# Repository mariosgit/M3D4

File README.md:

# M3D4

Majo's Mega Mixer Digital 4 devices. Simple.

# Status

Miniboard to test with FreeDSP. @alpha, not tested.

# What's this

Just another mixer thing.

# Cost

| part | euro | ... | # | sum |
|---|---|---|---|---|
| C108 | 2 | | 4 | 8
| SRC419x | 6,42  | SRC | 8 | 52 |
| ADAU1701 | 8,47 | DSP | 1 | 9 |
| sum | | | | **69** |

# Refs

CM108 symbol https://github.com/islandcontroller/fiberaudio-108

# License

### Hardware

<p xmlns:cc="http://creativecommons.org/ns#" >This work is licensed under <a href="https://creativecommons.org/licenses/by-nc-sa/4.0/?ref=chooser-v1" target="_blank" rel="license noopener noreferrer" style="display:inline-block;">CC BY-NC-SA 4.0</a></p>

### Software

MIT

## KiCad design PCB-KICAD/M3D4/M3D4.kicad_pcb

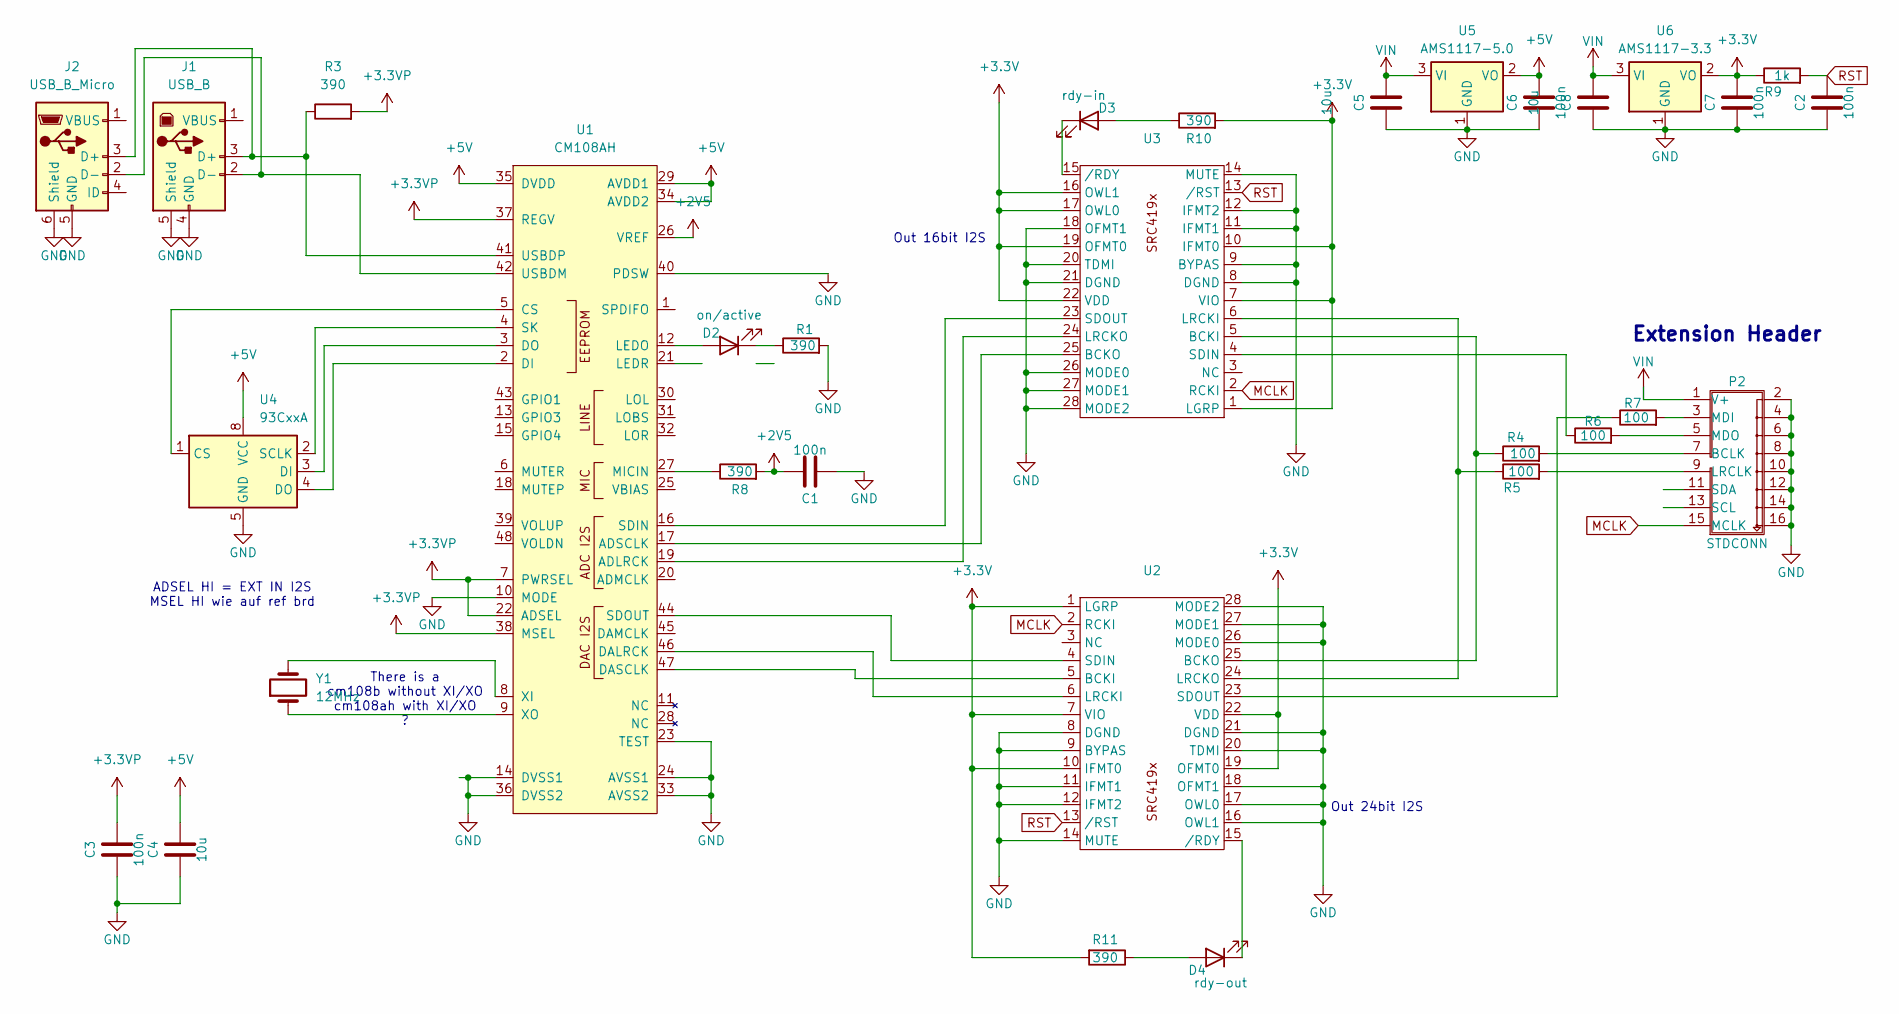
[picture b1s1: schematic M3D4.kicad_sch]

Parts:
C1, C2, C3, C6, C7: 100n; C_0603_1608Metric_Pad1.08x0.95mm_HandSolder
C4, C5: 10u; C_0603_1608Metric_Pad1.08x0.95mm_HandSolder
C8: 10u; C_1206_3216Metric_Pad1.33x1.80mm_HandSolder
D2: on/active; LED_0603_1608Metric_Pad1.05x0.95mm_HandSolder
D3: rdy-in; LED_0603_1608Metric_Pad1.05x0.95mm_HandSolder
D4: rdy-out; LED_0603_1608Metric_Pad1.05x0.95mm_HandSolder
J1: USB_B; USB_B_Lumberg_2411_02_Horizontal
J2: USB_B_Micro; USB_Micro-B_Amphenol_10103594-0001LF_Horizontal
P2: STDCONN; PinHeader_2x08_P2.54mm_Vertical
R1, R3, R8, R10, R11: 390; R_0603_1608Metric_Pad0.98x0.95mm_HandSolder
R4, R5, R6, R7: 100; R_0603_1608Metric_Pad0.98x0.95mm_HandSolder
R9: 1k; R_0603_1608Metric_Pad0.98x0.95mm_HandSolder
U1: CM108AH; LQFP-48_7x7mm_P0.5mm
U2, U3: SSOP-28_3.9x9.9mm_P0.635mm
U4: 93CxxA; SOIC-8-N7_3.9x4.9mm_P1.27mm
U5: AMS1117-5.0; SOT-223-3_TabPin2
U6: AMS1117-3.3; SOT-223-3_TabPin2
Y1: 12MHz; Crystal_SMD_HC49-SD_HandSoldering

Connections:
+2V5: C1.1, R8.2, U1.26 (VREF)
+3.3V: C7.1, R9.1, R10.2, R11.2, U2.1 (LGRP), U2.7 (VIO), U2.10 (IFMT0), U2.19 (OFMT0), U2.22 (VDD), U3.1 (LGRP), U3.7 (VIO), U3.10 (IFMT0), U3.16 (OWL1), U3.17 (OWL0), U3.19 (OFMT0), U3.22 (VDD), U6.2 (VO)
+3.3VP: C3.1, R3.2, U1.7 (PWRSEL), U1.22 (ADSEL), U1.37 (REGV), U1.38 (MSEL)
+5V: C4.1, C6.1, U1.29 (AVDD1), U1.34 (AVDD2), U1.35 (DVDD), U4.8 (VCC), U5.2 (VO)
GND: C1.2, C2.2, C3.2, C4.2, C5.2, C6.2, C7.2, C8.2, J1.4 (GND), J1.5 (Shield), J2.5 (GND), J2.6 (Shield), P2.2 (GND), P2.4 (GND), P2.6 (GND), P2.8 (GND), P2.10 (GND), P2.12 (GND), P2.14 (GND), P2.16 (GND), R1.2, U1.10 (MODE), U1.14 (DVSS1), U1.23 (TEST), U1.24 (AVSS1), U1.33 (AVSS2), U1.36 (DVSS2), U1.40 (PDSW), U2.8 (DGND), U2.9 (BYPAS), U2.11 (IFMT1), U2.12 (IFMT2), U2.14 (MUTE), U2.16 (OWL1), U2.17 (OWL0), U2.18 (OFMT1), U2.20 (TDMI), U2.21 (DGND), U2.26 (MODE0), U2.27 (MODE1), U2.28 (MODE2), U3.8 (DGND), U3.9 (BYPAS), U3.11 (IFMT1), U3.12 (IFMT2), U3.14 (MUTE), U3.18 (OFMT1), U3.20 (TDMI), U3.21 (DGND), U3.26 (MODE0), U3.27 (MODE1), U3.28 (MODE2), U4.5 (GND), U5.1 (GND), U6.1 (GND)
MCLK: P2.15 (MCLK), U2.2 (RCKI), U3.2 (RCKI)
unnamed: D2.2 (A), U1.12 (LEDO)
unnamed: D2.1 (K), R1.1
unnamed: D3.2 (A), R10.1
unnamed: D3.1 (K), U3.15 (/RDY)
unnamed: D4.2 (A), R11.1
unnamed: D4.1 (K), U2.15 (/RDY)
unnamed: J1.3 (D+), J2.3 (D+), R3.1, U1.41 (USBDP)
unnamed: J1.2 (D-), J2.2 (D-), U1.42 (USBDM)
unnamed: P2.7 (BCLK), R4.2
unnamed: P2.9 (LRCLK), R5.2
unnamed: P2.3 (MDI), R7.2
unnamed: P2.5 (MDO), R6.2
unnamed: U1.19 (ADLRCK), U3.24 (LRCKO)
unnamed: U1.17 (ADSCLK), U3.25 (BCKO)
unnamed: U1.5 (CS), U4.1 (CS)
unnamed: U1.46 (DALRCK), U2.6 (LRCKI)
unnamed: U1.47 (DASCLK), U2.5 (BCKI)
unnamed: U1.2 (DI), U4.4 (DO)
unnamed: U1.3 (DO), U4.3 (DI)
unnamed: R8.1, U1.27 (MICIN)
unnamed: U1.16 (SDIN), U3.23 (SDOUT)
unnamed: U1.44 (SDOUT), U2.4 (SDIN)
unnamed: U1.4 (SK), U4.2 (SCLK)
unnamed: U1.8 (XI), Y1.2
unnamed: U1.9 (XO), Y1.1
unnamed: R4.1, U2.25 (BCKO), U3.5 (BCKI)
unnamed: R5.1, U2.24 (LRCKO), U3.6 (LRCKI)
unnamed: R7.1, U2.23 (SDOUT)
unnamed: R6.1, U3.4 (SDIN)
RST: C2.1, R9.2, U2.13 (/RST), U3.13 (/RST)
VIN: C5.1, C8.1, P2.1 (V+), U5.3 (VI), U6.3 (VI)

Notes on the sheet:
Out 16bit I2S
ADSEL HI = EXT IN I2S MSEL HI wie auf ref brd
Extension Header
There is a cm108b without XI/XO cm108ah with XI/XO ?
Out 24bit I2S

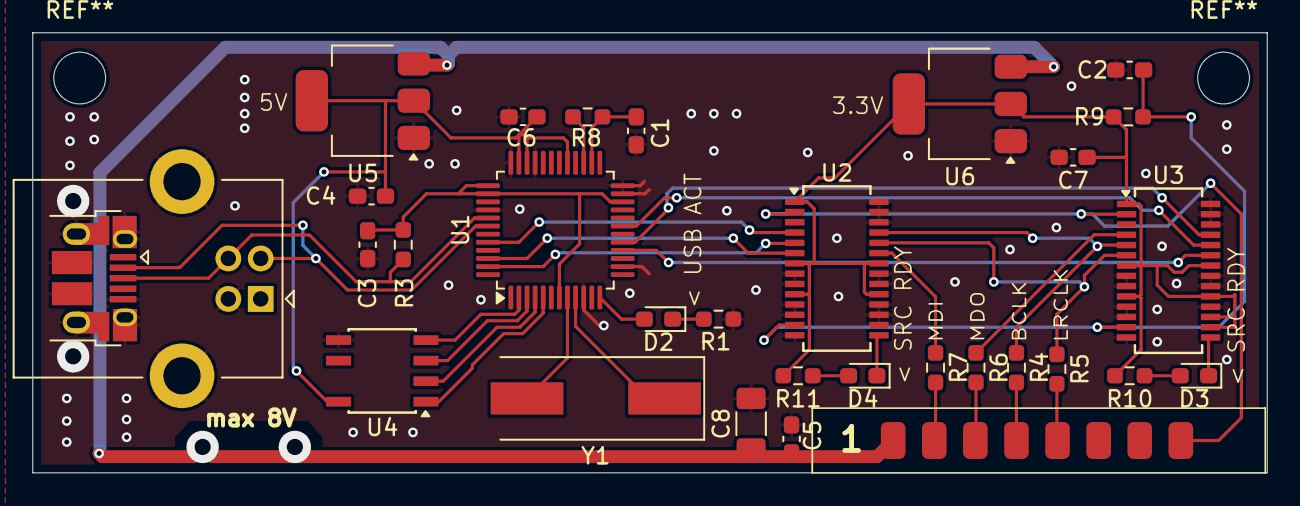
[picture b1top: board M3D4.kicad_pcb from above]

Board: 2 copper layers, 76.3 x 27.2 mm, 31 parts (0 on the bottom side), 37 nets.

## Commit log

2024-06-17 pcb alpha 0.0.1
2024-06-19 First test board.
2024-06-26 Fixed connector bottom pads.
2024-07-02 No zip's please.
